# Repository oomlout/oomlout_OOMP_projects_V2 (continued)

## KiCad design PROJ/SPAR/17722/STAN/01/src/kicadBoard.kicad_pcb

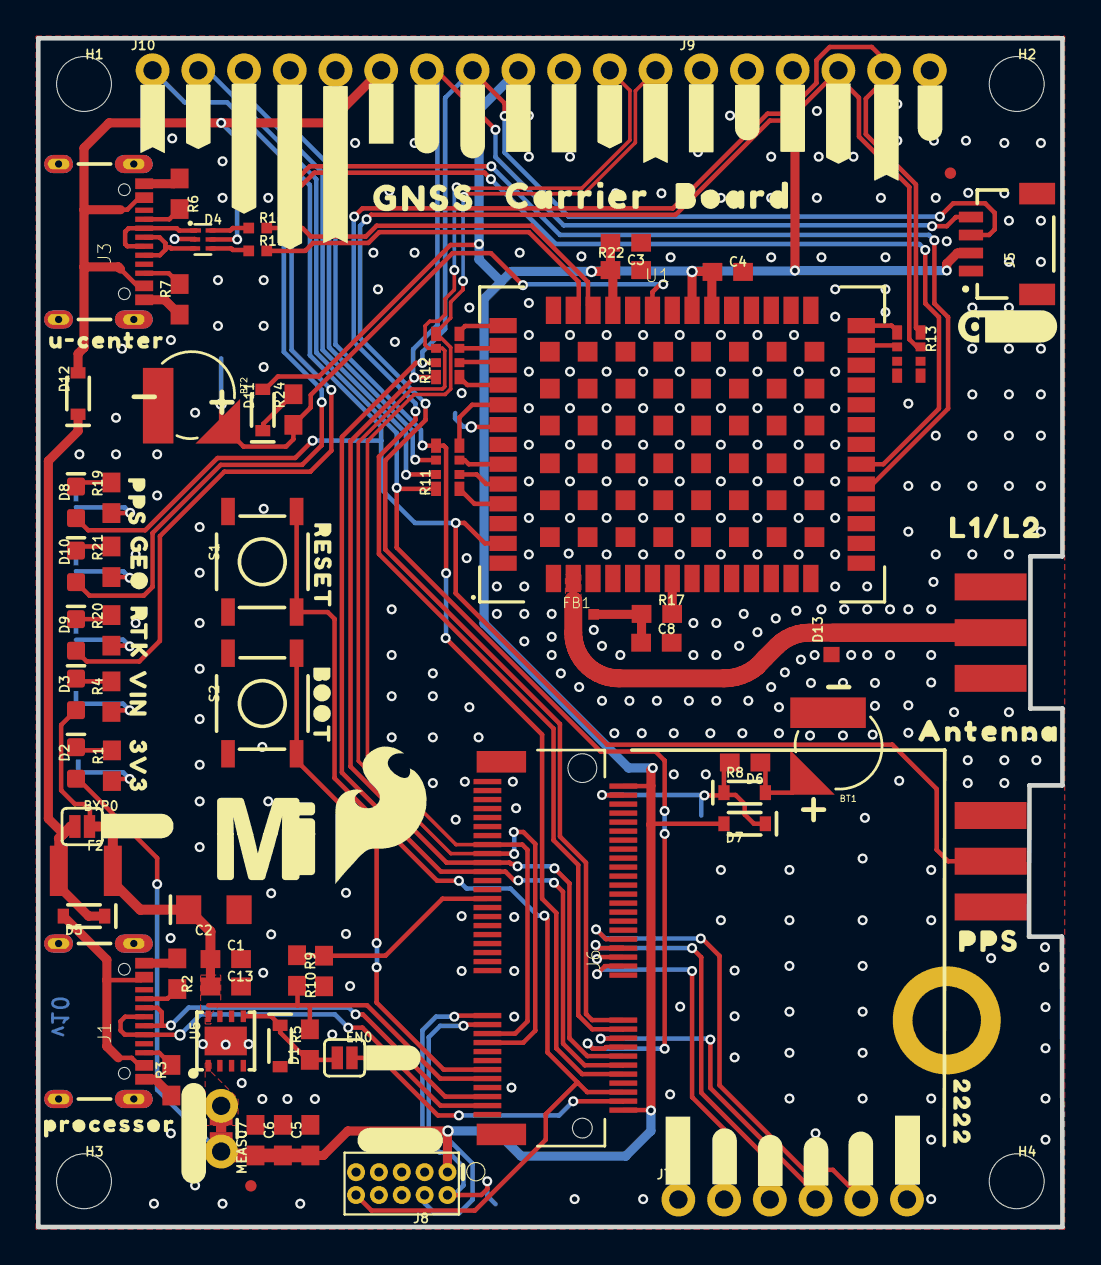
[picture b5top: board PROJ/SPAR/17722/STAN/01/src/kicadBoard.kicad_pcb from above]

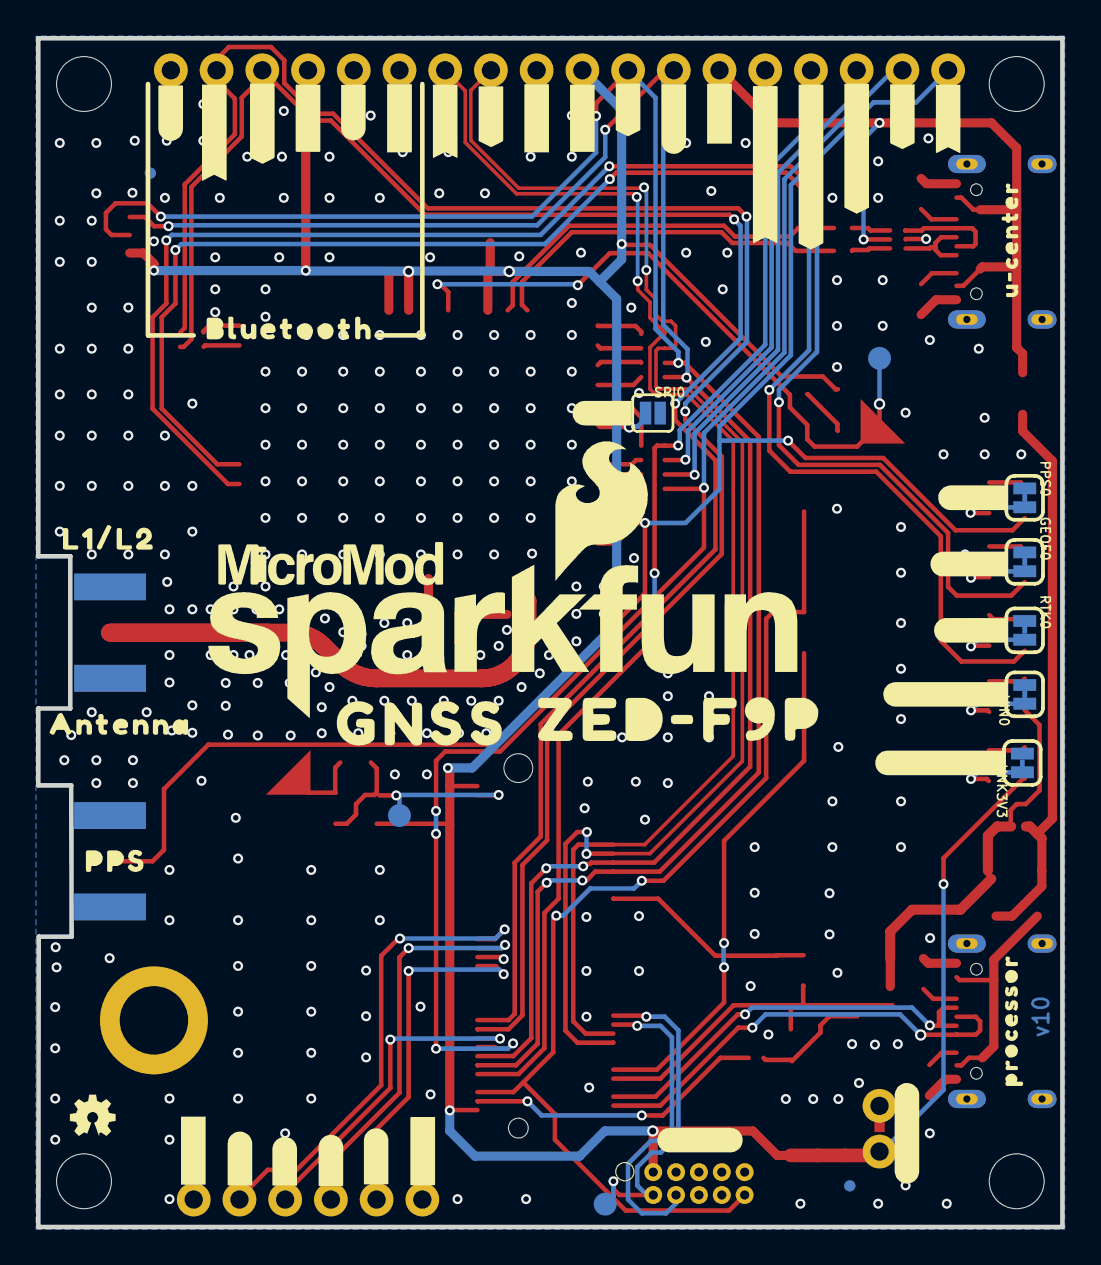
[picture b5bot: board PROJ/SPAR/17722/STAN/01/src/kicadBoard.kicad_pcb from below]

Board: 2 copper layers, 56.9 x 66.0 mm, 174 parts (54 on the bottom side), 71 nets.

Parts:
BT1: ML414H; ML414H_IV01E
BT2: ML414H_IV01E_BATTERY; ML414H_IV01E
BYP0: JUMPER-SMT_2_NO_SILK; SMT-JUMPER_2_NO_SILK
C1, C3, C4, C6: 0.1uF; 0603
C2: 10uF; EIA3216
C5: 1.0uF; 0603
C7, C13: 0.22uF; 0603
C8: 47pF; 0603
D1: 3.3V; SOD-323
D2, D3: RED; LED-0603
D4: PRTR5V0U2F; SOT886
D5, D6, D12: 3A/10V/280mV; SOD-323
D7: 1A/23V/620mV; SOD-323
D8, D9, D10: BLUE; LED-0603
D11: 0.5A/40V/420mV; SOD-323
D13: PESD0402; 0402
E1: ANTENNA-SMA-GROUNDEDEDGE_SMA; SMA-EDGE
EN0: JUMPER-SMT_2_NO_SILK; SMT-JUMPER_2_NO_SILK
F2: 6V/2A; 1210
FB1: FERRITE_BEAD-120_OHM-0402T; 0402-TIGHT
FD1, FD2, FD3, FD4: FIDUCIALUFIDUCIAL; FIDUCIAL-MICRO
FRAME1: FRAME-LEDGER; CREATIVE_COMMONS
GEOF0: JUMPER-SMT_2_NC_TRACE_SILK; SMT-JUMPER_2_NC_TRACE_SILK
H1, H2, H3, H4: STAND-OFFTIGHT; STAND-OFF-TIGHT
H5: STAND-OFF-REFLOW-M2.5_2.5MM_TALL; STAND-OFF-REFLOW-M2.5
J1, J3: USB-C-16P-2LAYER-PADS
J4: U.FL; SMA-EDGE
J5: QWIIC_RIGHT_ANGLE; JST04_1MM_RA
J6: MICROMOD-2222-C; M.2-CONNECTOR-E
J7, J9: 1X06_NO_SILK
J8: JTAG; 2X5-PTH-1.27MM
J10: 1X12_NO_SILK
LOGO1: SFE_LOGO_NAME_FLAME.3_INCH; SFE_LOGO_NAME_FLAME_.3
LOGO3: OSHW-LOGOMINI; OSHW-LOGO-MINI
MEAS0: JUMPER-COMBO_2_NC_TRACE; COMBO-JUMPER_2_NC_TRACE
PPS0: JUMPER-SMT_2_NC_TRACE_SILK; SMT-JUMPER_2_NC_TRACE_SILK
R1, R4, R8, R19, R20, R21: 1k; 0603
R2, R3, R6, R7: 5.1k; 0603
R5, R22: 100k; 0603
R9: 10k; 0603
R10: 20k; 0603
R11, R12, R13: 33; 1206_RA
R15, R16: 27OHM; 0402-TIGHT
R17: 33; 0603
R24: 3.3k; 0603
RTK0: JUMPER-SMT_2_NC_TRACE_SILK; SMT-JUMPER_2_NC_TRACE_SILK
S1: Reset; TACTILE_SWITCH_SMD_5.2MM
S2: BOOT; TACTILE_SWITCH_SMD_5.2MM
SPI0: JUMPER-SMT_2_NO_SILK; SMT-JUMPER_2_NO_SILK
TP1, TP2, TP3: TEST-POINT3X5; PAD.03X.05
U1: U-BLOX_ZED-F9P; ZED-F9P
U5: AP7361C-33; UDFN-8
U$1: ##SFBOOT##13
U$2: ##SFBOOT##8
U$3, U$4, U$31, U$32: #3V3#1
U$5: #RESET10
U$6, U$7, U$33, U$34, U$64, U$65, U$66, U$77, U$78: #GND#0
U$8: ##TX_READY##13
U$9: #PPS#6
U$10: #SCL#1
U$11: #RXI2#9
U$12: #SDA#0
U$13: #TXO#5
U$14: #RXI#6
U$15: #TXO2#9
U$16: PPS15
U$17, U$35: #VIN#13
U$18: GEO15
U$19: PPS14
U$20: RTK16
U$21: ANTENNA16
U$22: L1#L216
U$23: #GEO#9
U$24: ##TX_READY##7
U$25: MICROMOD_LOGO_.5
U$26: #PPS#10
U$27: #RTK#8
U$28: ##CS##9
U$29: #INT#4
U$30: #SPI#11
U$36: #INT#10
U$37: #PPS#3
U$38: #TXO2#10
U$39: #BYP#8
U$40: #RXI2#10
U$41: MICROMOD_MI_LOGO_1
U$42, U$132: #MEAS#10
U$43: BOOT10
U$44: ZED#F9P19
U$45: GNSS21
U$46: #CLK#7
U$47: #SDO#9
U$48: #EN#0
U$49: U#CENTER20
U$50: QWIIC_5.5MM
U$51, U$131: #SWD#10
U$52, U$73: PROCESSOR23
U$53: #SDI#11
U$54: BLUETOOTH24
U$55, U$83: #NC#4
U$56: U#CENTER22
U$57: #A0#14
U$58: L1#L217
U$59: ANTENNA17
U$60: PPS16
U$61: ##ZED_RESET##9
U$62: ##ZED_RESET##14
U$63: SFE_LOGO_FLAME_.3
U$67: #A0#8
U$68: VIN3
U$69: 3V34
U$70: #A1#8
U$71: #D1#8
U$72: #D2#8
U$74: #A1#14
U$75: #D1#14
U$76: #D2#14
U$79: GNSS501
U$80: CARRIER502
U$81: BOARD503
U$82: 2222501
U$84, U$85: #NC#5
U$133: #VIN_LED#10
U$134: #3V3_LED#10
UNK3V3: JUMPER-SMT_2_NC_TRACE_SILK; SMT-JUMPER_2_NC_TRACE_SILK
VIN0: JUMPER-SMT_2_NC_TRACE_SILK; SMT-JUMPER_2_NC_TRACE_SILK

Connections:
3.3V: C3.1, C4.1, C5.1, C6.1, C7.1, D2.A, D7.A, D11.A, J5.2, J6.2, J6.74, J8.1, J9.3, J10.9, MEAS0.2, MEAS0.4, R22.2, U1.33, U1.34, U1.38
3.3V_EN: D1.C, EN0.1, R5.1, U5.5
A0: J6.34, J7.2
A1: J6.38, J7.3
D1: J6.18, J7.4
D_SEL: SPI0.1, U1.47
G0/D2: J6.40, J7.5
GEO_STAT: D10.A, U1.19
GND: BT1.-, BT2.-, C1.2, C2.-, C3.2, C4.2, C5.2, C6.2, C7.2, C8.2, C13.2, D1.A, D4.2, D13.1, E1.GND@0, E1.GND@1, E1.GND@2, E1.GND@3, GEOF0.1, H5.1, J1.GND, J1.GND2, J3.GND, J3.GND2, J4.GND@0, J4.GND@1, J4.GND@2, J4.GND@3, J5.1, J6.1, J6.7, J6.33, J6.36, J6.39, J6.45, J6.75, J7.1, J7.6, J8.3, J8.5, J8.9, J9.1, J10.10, PPS0.1, R2.1, R3.1, R6.1, R7.1, R9.1, R22.1, RTK0.1, S1.1, S1.2, S2.1, S2.2, SPI0.2, U1.1, U1.3, U1.12, U1.14, U1.32, U1.37, U1.41, U1.48, U1.55, U1.56, U1.57, U1.58, U1.59, U1.60, U1.61, U1.62, U1.63, U1.64, U1.65, U1.66, U1.67, U1.68, U1.69, U1.70, U1.71, U1.72, U1.73, U1.74, U1.75, U1.76, U1.77, U1.78, U1.79, U1.80, U1.81, U1.82, U1.83, U1.84, U1.85, U1.86, U1.87, U1.88, U1.89, U1.90, U1.91, U1.92, U1.93, U1.94, U1.95, U1.96, U1.97, U1.98, U1.99, U1.100, U1.101, U1.102, U5.4, U5.EP, UNK3V3.2, VIN0.2
INT: J6.16, J10.2, R11.P8
unnamed: D2.C, R1.2
unnamed: R4.1, VIN0.1
unnamed: R1.1, UNK3V3.1
unnamed: D3.C, R4.2
unnamed: EN0.2, J6.4
unnamed: J3.A5, R6.2
unnamed: J3.B5, R7.2
unnamed: R20.1, RTK0.2
unnamed: D4.6, R16.1
unnamed: J1.A5, R2.2
unnamed: J1.B5, R3.2
unnamed: D4.3, J3.A6, J3.B6
unnamed: D4.1, J3.A7, J3.B7
unnamed: BT1.+, D6.A, R8.1
unnamed: R11.P1, U1.51
unnamed: R11.P2, U1.50
unnamed: D4.4, R15.1
unnamed: C8.1, FB1.2, R17.1
unnamed: R11.P3, U1.49
unnamed: R11.P4, U1.46
unnamed: R12.P1, U1.45
unnamed: R12.P2, U1.44
unnamed: R12.P3, U1.43
unnamed: R12.P4, U1.42
unnamed: R13.P1, U1.27
unnamed: R13.P2, U1.26
unnamed: PPS0.2, R19.1
unnamed: D8.C, R19.2
unnamed: D9.C, R20.2
unnamed: D11.C, R24.2
unnamed: GEOF0.2, R21.1
unnamed: D10.C, R21.2
OUT_MEAS: MEAS0.1, MEAS0.3, U5.1
PPS: D8.A, E1.SIG, J10.1, U1.53
RF_IN: D13.2, FB1.1, J4.SIG, U1.2
RTC_3V: D6.C, D7.C, J6.72, R8.2, TP1.1
RTK_STAT: D9.A, U1.20
RXI2: J6.22, J9.4, R13.P7
RXI/SDI: J6.17, J6.59, J10.11, R12.P6
SCL/SCK: J5.4, J6.14, J6.57, J10.7, R12.P8
SDA/~CS: J5.3, J6.12, J6.55, J10.8, R12.P7
SWDCK: J6.21, J8.4
SWDIO: J6.23, J8.2, TP2.1
TXO2: J6.20, J9.5, R13.P8
TXO/SDO: J6.19, J6.61, J10.12, R12.P5
TX_READY: J6.10, J10.5, R11.P5
USB_N: J1.A7, J1.B7, J6.5
USB_P: J1.A6, J1.B6, J6.3
VIN: BYP0.2, C1.1, C2.+, C13.1, D3.A, F2.2, J6.9, R5.2, R10.2, U5.8
VIN/3: J6.49, R9.2, R10.1
V_BATT: BT2.+, R24.1, TP3.1, U1.36
V_FUSE: BYP0.1, D5.C, D12.C, F2.1
V_RF: R17.2, U1.7
V_USB: D5.A, J1.VBUS1, J1.VBUS2
V_USB_2: D4.5, D12.A, J3.VBUS1, J3.VBUS2, J10.6
ZED_USB_N: R16.2, U1.39
ZED_USB_P: R15.2, U1.40
~BOOT: J6.11, S2.3, S2.4
~RESET: J6.6, J8.10, S1.3, S1.4
~SAFEBOOT: J10.3, R11.P7
~ZED_RESET: J10.4, R11.P6

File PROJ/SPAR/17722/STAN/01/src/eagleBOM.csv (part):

"Part";"Value";"Device";"Package";"Description";"DESIGNER";"DIGIKEY_PART";"MOUSE_PART";"PROD_ID";"REV";"VALUE";
"3V3";"JUMPER-SMT_2_NC_TRACE_SILK";"JUMPER-SMT_2_NC_TRACE_SILK";"SMT-JUMPER_2_NC_TRACE_SILK";"Normally closed trace jumper";"";"";"";"";"";"";
"BT1";"ML414H";"ML414H_IV01E_BATTERY";"ML414H_IV01E";"SEIKO ML414H-IV01E Reflowable Lithium Battery";"";"";"";"BATT-14267";"";"";
"BT2";"ML414H_IV01E_BATTERY";"ML414H_IV01E_BATTERY";"ML414H_IV01E";"SEIKO ML414H-IV01E Reflowable Lithium Battery";"";"";"";"BATT-14267";"";"";
"BYP";"JUMPER-SMT_2_NO_SILK";"JUMPER-SMT_2_NO_SILK";"SMT-JUMPER_2_NO_SILK";"Normally open jumper";"";"";"";"";"";"";
"C1";"0.1uF";"0.1UF-0603-25V-(+80/-20%)";"0603";"0.1µF ceramic capacitors";"";"";"";"CAP-00810";"";"0.1uF";
"C2";"10uF";"10UF-POLAR-EIA3216-16V-10%(TANT)";"EIA3216";"10.0µF polarized capacitors";"";"";"";"CAP-00811";"";"10uF";
"C3";"0.1uF";"0.1UF-0603-25V-5%";"0603";"0.1µF ceramic capacitors";"";"";"";"CAP-08604";"";"0.1uF";
"C4";"0.1uF";"0.1UF-0603-25V-5%";"0603";"0.1µF ceramic capacitors";"";"";"";"CAP-08604";"";"0.1uF";
"C5";"1.0uF";"1.0UF-0603-16V-10%";"0603";"1µF ceramic capacitors";"";"";"";"CAP-00868";"";"1.0uF";
"C6";"0.1uF";"0.1UF-0603-25V-(+80/-20%)";"0603";"0.1µF ceramic capacitors";"";"";"";"CAP-00810";"";"0.1uF";
"C7";"0.22uF";"0.22UF-0603-25V-10%";"0603";"0.22µF ceramic capacitors";"";"";"";"CAP-07822";"";"0.22uF";
"C8";"47pF";"47PF-0603-50V-5%";"0603";"47pF ceramic capacitors";"";"";"";"CAP-08913";"";"47pF";
"C13";"0.22uF";"0.22UF-0603-25V-10%";"0603";"0.22µF ceramic capacitors";"";"";"";"CAP-07822";"";"0.22uF";
"D1";"3.3V";"DIODE-ZENER-MM3Z3V3T1G";"SOD-323";"Zener Diode";"";"";"";"DIO-11284";"";"3.3V";
"D2";"RED";"LED-RED0603";"LED-0603";"Red SMD LED";"";"";"";"DIO-00819";"";"RED";
"D3";"RED";"LED-RED0603";"LED-0603";"Red SMD LED";"";"";"";"DIO-00819";"";"RED";
"D4";"PRTR5V0U2F";"PRTR5V0U2F";"SOT886";"A small ESD protection device. Most commonly used on USB D+/D- signals to protect large, expensive, or especially sensitive USB enabled devices.";"";"";"";"DIO-14084";"";"";
"D5";"3A/10V/280mV";"DIODE-SCHOTTKY-BAT60A";"SOD-323";"Schottky diode";"";"";"";"DIO-14072";"";"3A/10V/280mV";
"D6";"3A/10V/280mV";"DIODE-SCHOTTKY-BAT60A";"SOD-323";"Schottky diode";"";"";"";"DIO-14072";"";"3A/10V/280mV";
"D7";"1A/23V/620mV";"DIODE-SCHOTTKY-BAT20J";"SOD-323";"Schottky diode";"";"";"";"DIO-11623";"";"1A/23V/620mV";
"D8";"BLUE";"LED-BLUE0603";"LED-0603";"Blue SMD LED";"";"";"";"DIO-08575";"";"BLUE";
"D9";"BLUE";"LED-BLUE0603";"LED-0603";"Blue SMD LED";"";"";"";"DIO-08575";"";"BLUE";
"D10";"BLUE";"LED-BLUE0603";"LED-0603";"Blue SMD LED";"";"";"";"DIO-08575";"";"BLUE";
"D11";"0.5A/40V/420mV";"DIODE-SCHOTTKY-PMEG4005EJ";"SOD-323";"Schottky diode";"";"";"";"DIO-10955";"";"0.5A/40V/420mV";
"D12";"3A/10V/280mV";"DIODE-SCHOTTKY-BAT60A";"SOD-323";"Schottky diode";"";"";"";"DIO-14072";"";"3A/10V/280mV";
"D13";"PESD0402";"PESD0402";"0402";"ESD protection diode";"";"PESD0402-140CT-ND";"650-PESD0402-140";"DIO-15359";"";"";
"E1";"ANTENNA-SMA-GROUNDEDEDGE_SMA";"ANTENNA-SMA-GROUNDEDEDGE_SMA";"SMA-EDGE";"SMA Antenna Connector w/ Ground";"";"";"";"CONN-08289";"";"";
"EN";"JUMPER-SMT_2_NO_SILK";"JUMPER-SMT_2_NO_SILK";"SMT-JUMPER_2_NO_SILK";"Normally open jumper";"";"";"";"";"";"";
"F2";"6V/2A";"PPTC_6V2A";"1210";"Resettable Fuse PPTC";"";"";"";"RES-14313";"";"6V/2A";
"FB1";"FERRITE_BEAD-120_OHM-0402T";"FERRITE_BEAD-120_OHM-0402T";"0402-TIGHT";"Ferrite Bead (blocks, cores, rings, chokes, etc.)";"";"";"";"NDUC-14206";"";"";
"FD1";"FIDUCIALUFIDUCIAL";"FIDUCIALUFIDUCIAL";"FIDUCIAL-MICRO";"Fiducial Alignment Points";"";"";"";"";"";"";
"FD2";"FIDUCIALUFIDUCIAL";"FIDUCIALUFIDUCIAL";"FIDUCIAL-MICRO";"Fiducial Alignment Points";"";"";"";"";"";"";
"FD3";"FIDUCIALUFIDUCIAL";"FIDUCIALUFIDUCIAL";"FIDUCIAL-MICRO";"Fiducial Alignment Points";"";"";"";"";"";"";
"FD4";"FIDUCIALUFIDUCIAL";"FIDUCIALUFIDUCIAL";"FIDUCIAL-MICRO";"Fiducial Alignment Points";"";"";"";"";"";"";
"FRAME1";"FRAME-LEDGER";"FRAME-LEDGER";"CREATIVE_COMMONS";"Schematic Frame - Ledger";"";"";"";"";"";"";
"GEOF";"JUMPER-SMT_2_NC_TRACE_SILK";"JUMPER-SMT_2_NC_TRACE_SILK";"SMT-JUMPER_2_NC_TRACE_SILK";"Normally closed trace jumper";"";"";"";"";"";"";
"H1";"STAND-OFFTIGHT";"STAND-OFFTIGHT";"STAND-OFF-TIGHT";"Stand Off";"";"";"";"";"";"";
"H2";"STAND-OFFTIGHT";"STAND-OFFTIGHT";"STAND-OFF-TIGHT";"Stand Off";"";"";"";"";"";"";
"H3";"STAND-OFFTIGHT";"STAND-OFFTIGHT";"STAND-OFF-TIGHT";"Stand Off";"";"";"";"";"";"";
"H4";"STAND-OFFTIGHT";"STAND-OFFTIGHT";"STAND-OFF-TIGHT";"Stand Off";"";"";"";"";"";"";
"H5";"STAND-OFF-REFLOW-M2.5_2.5MM_TALL";"STAND-OFF-REFLOW-M2.5_2.5MM_TALL";"STAND-OFF-REFLOW-M2.5";"Stand Off Reflow Compatible";"";"";"";"HW-14899";"";"";
"J1";"";"USB_C_2-LAYER_PADS";"USB-C-16P-2LAYER-PADS";"USB Type C 16Pin Connector";"";"";"";"CONN-14122";"";"";
"J3";"";"USB_C_2-LAYER_PADS";"USB-C-16P-2LAYER-PADS";"USB Type C 16Pin Connector";"";"";"";"CONN-14122";"";"";
"J4";"U.FL";"ANTENNA-SMA-GROUNDEDEDGE_SMA";"SMA-EDGE";"SMA Antenna Connector w/ Ground";"";"";"";"CONN-08289";"";"";
"J5";"QWIIC_RIGHT_ANGLE";"QWIIC_CONNECTORJS-1MM";"JST04_1MM_RA";"SparkFun I2C Standard Qwiic Connector";"";"";"";"CONN-13694";"";"QWIIC_RIGHT_ANGLE";
"J6";"MICROMOD-2222-C";"MICROMOD-2222-C";"M.2-CONNECTOR-E";"MicroMod Connector";"";"";"";"CONN-14877";"";"";
"J7";"";"CONN_06NO_SILK_NO_POP";"1X06_NO_SILK";"Multi connection point. Often used as Generic Header-pin footprint for 0.1 inch spaced/style header connections";"";"";"";"";"";"";
"J8";"JTAG";"CORTEX_JTAG_DEBUG_MINIMUM_PTH";"2X5-PTH-1.27MM";"Cortex Debug Connector - 10 pin";"";"";"";"";"";"";
"J9";"";"CONN_06NO_SILK_NO_POP";"1X06_NO_SILK";"Multi connection point. Often used as Generic Header-pin footprint for 0.1 inch spaced/style header connections";"";"";"";"";"";"";
"J10";"";"CONN_12NO_SILK";"1X12_NO_SILK";"Multi connection point. Often used as Generic Header-pin footprint for 0.1 inch spaced/style header connections";"";"";"";"";"";"";
"LOGO1";"SFE_LOGO_NAME_FLAME.3_INCH";"SFE_LOGO_NAME_FLAME.3_INCH";"SFE_LOGO_NAME_FLAME_.3";"SparkFun Font Logo w/ Flame";"";"";"";"";"";"";
"LOGO3";"OSHW-LOGOMINI";"OSHW-LOGOMINI";"OSHW-LOGO-MINI";"Open-Source Hardware (OSHW) Logo";"";"";"";"";"";"";
"MEAS";"JUMPER-COMBO_2_NC_TRACE";"JUMPER-COMBO_2_NC_TRACE";"COMBO-JUMPER_2_NC_TRACE";"";"";"";"";"";"";"";
"PPS";"JUMPER-SMT_2_NC_TRACE_SILK";"JUMPER-SMT_2_NC_TRACE_SILK";"SMT-JUMPER_2_NC_TRACE_SILK";"Normally closed trace jumper";"";"";"";"";"";"";
"R1";"1k";"1KOHM-0603-1/10W-1%";"0603";"1kΩ resistor";"";"";"";"RES-07856";"";"1k";
"R2";"5.1k";"5.1KOHM5.1KOHM-0603-1/10W-1%";"0603";"";"";"";"";"RES-12083";"";"5.1k";
"R3";"5.1k";"5.1KOHM5.1KOHM-0603-1/10W-1%";"0603";"";"";"";"";"RES-12083";"";"5.1k";
"R4";"1k";"1KOHM-0603-1/10W-1%";"0603";"1kΩ resistor";"";"";"";"RES-07856";"";"1k";
"R5";"100k";"100KOHM-0603-1/10W-1%";"0603";"100kΩ resistor";"";"";"";"RES-07828";"";"100k";
"R6";"5.1k";"5.1KOHM5.1KOHM-0603-1/10W-1%";"0603";"";"";"";"";"RES-12083";"";"5.1k";
"R7";"5.1k";"5.1KOHM5.1KOHM-0603-1/10W-1%";"0603";"";"";"";"";"RES-12083";"";"5.1k";
"R8";"1k";"1KOHM-0603-1/10W-1%";"0603";"1kΩ resistor";"";"";"";"RES-07856";"";"1k";
"R9";"10k";"10KOHM-0603-1/10W-1%";"0603";"10kΩ resistor";"";"";"";"RES-00824";"";"10k";
"R10";"20k";"20KOHM-0603-1/10W-1%";"0603";"20kΩ resistor";"";"";"";"RES-09383";"";"20k";
"R11";"33";"33OHM_RA-1206-1/16W-5%";"1206_RA";"EXB-38V330JV";"";"";"";"RES-15081";"";"33";
"R12";"33";"33OHM_RA-1206-1/16W-5%";"1206_RA";"EXB-38V330JV";"";"";"";"RES-15081";"";"33";
"R13";"33";"33OHM_RA-1206-1/16W-5%";"1206_RA";"EXB-38V330JV";"";"";"";"RES-15081";"";"33";
"R15";"27OHM";"27OHM";"0402-TIGHT";"27Ω resistor";"";"";"";"RES-15238";"";"";
"R16";"27OHM";"27OHM";"0402-TIGHT";"27Ω resistor";"";"";"";"RES-15238";"";"";
"R17";"33";"33OHM-0603-1/10W-1%";"0603";"33Ω resistor";"";"";"";"RES-08270";"";"33";
"R19";"1k";"1KOHM-0603-1/10W-1%";"0603";"1kΩ resistor";"";"";"";"RES-07856";"";"1k";
"R20";"1k";"1KOHM-0603-1/10W-1%";"0603";"1kΩ resistor";"";"";"";"RES-07856";"";"1k";
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
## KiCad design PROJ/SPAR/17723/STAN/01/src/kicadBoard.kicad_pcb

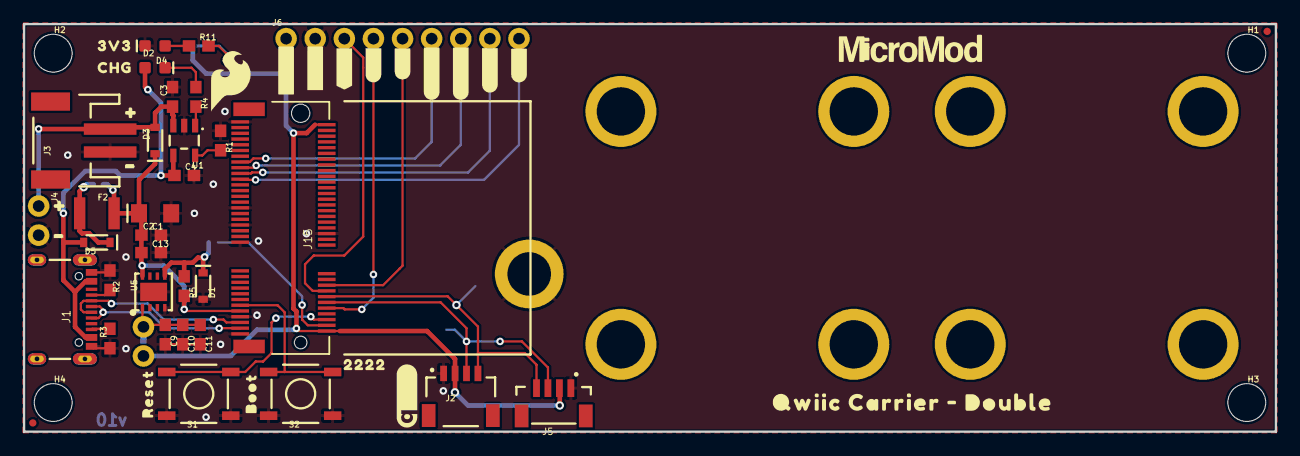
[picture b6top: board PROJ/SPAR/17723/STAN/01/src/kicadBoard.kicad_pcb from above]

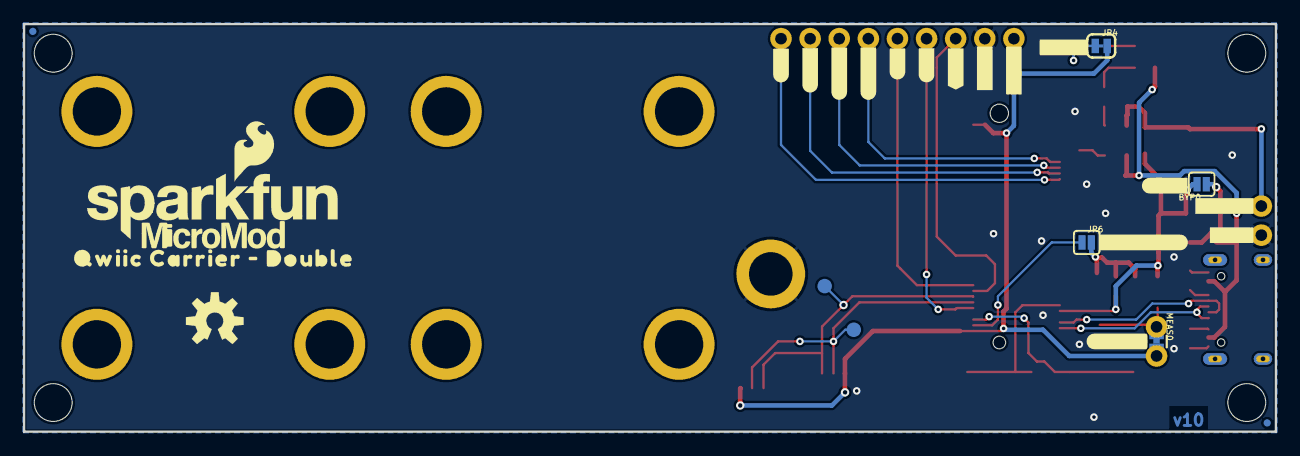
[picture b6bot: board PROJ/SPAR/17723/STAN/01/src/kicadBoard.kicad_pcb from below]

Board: 2 copper layers, 109.2 x 35.6 mm, 90 parts (27 on the bottom side), 29 nets.

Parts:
BYP0: JUMPER-SMT_2_NO_SILK; SMT-JUMPER_2_NO_SILK
C1: 0.1uF; 0603
C2: 10uF; EIA3216
C3, C4: 4.7uF; 0603
C9: 10uF; 0603
C10: 1.0uF; 0603
C11, C13: 0.22uF; 0603
D1: 3.3V; SOD-323
D2: RED; LED-0603
D3, D5: 3A/10V/280mV; SOD-323
D4: Yellow; LED-0603
F2: 6V/2A; 1210
FD1, FD2, FD3, FD4: FIDUCIALUFIDUCIAL; FIDUCIAL-MICRO
FRAME1: FRAME-LEDGER; CREATIVE_COMMONS
H1, H2, H3, H4: STAND-OFF
H5: STAND-OFF-REFLOW2.5MM_TALL; STAND-OFF-REFLOW-M2.5
J1: USB-C-16P-2LAYER-PADS
J2: QWIIC_RIGHT_ANGLE; JST04_1MM_RA
J3: JST-2-SMD
J4: 1X02_NO_SILK
J5: Vertical Qwiic Connector; JST04_1MM_VERT
J6: 1X09_NO_SILK
J15: MICROMOD-2222-C; M.2-CONNECTOR-E
JP4: 3V3 LED; SMT-JUMPER_2_NC_TRACE_SILK
JP6: VE; SMT-JUMPER_2_NO_SILK
LOGO1: SFE_LOGO_NAME_FLAME.2_INCH; SFE_LOGO_NAME_FLAME_.2
LOGO2: QWIIC_LOGO_CONNECTOR; QWIIC_5.5MM
LOGO3: OSHW-LOGOM; OSHW-LOGO-M
MEAS0: COMBO-JUMPER_2_NC_TRACE
R1: 2.2k; 0603
R2, R3: 5.1k; 0603
R4, R11: 1k; 0603
R5: 100k; 0603
S1: Reset; TACTILE_SWITCH_SMD_5.2MM
S2: BOOT; TACTILE_SWITCH_SMD_5.2MM
TP1, TP2: TEST-POINT3X5; PAD.03X.05
U1: MCP73831; SOT23-5
U5: AP7361C-33FGEUDFN-8; UDFN-8
U$1: #3#3V_EN#0
U$2, U$5: QWIIC_BOARD_OUTLINESTANDOFF; QWIIC_BOARD_MOUNT_SMD_STANDOFFS
U$3: 3V30
U$4: CHG0
U$6, U$35, U$38: #3#3V#0
U$7: #BYP#0
U$8, U$14, U$33: #GND#0
U$9: #MEAS#0
U$10, U$13: QWIIC_CARRIER_#_DOUBLE0
U$11, U$32, U$36, U$37: #0
U$12: #VBAT#0
U$15, U$16: ##INT##0
U$17, U$18: #D0#0
U$20, U$21: #D1#0
U$22, U$23: #CIPO#0
U$24, U$25: #COPI#0
U$26, U$27: #SCK#0
U$28, U$29: ##CS##0
U$30: RESET0
U$31: BOOT0
U$34: 22220
U$44: SFE_LOGO_FLAME_.2
U$67, U$68: MICROMOD_LOGO_.5

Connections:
3.3V: J2.2, J5.2, J6.1, J15.2, J15.74, JP4.2, MEAS0.2, MEAS0.4
3.3V_EN: J15.4, JP6.1
D0: J6.4, J15.10
D1: J6.5, J15.18
GND: C1.2, C2.-, C3.2, C4.2, C9.2, C10.2, C11.2, C13.2, D1.A, D2.C, H5.1, J1.GND, J1.GND2, J2.1, J3.1, J4.2, J5.1, J6.2, J15.1, J15.7, J15.33, J15.36, J15.39, J15.45, J15.75, R1.1, R2.1, R3.1, S1.1, S1.2, S2.1, S2.2, U1.2, U5.4, U5.EP
I2C_~INT: J6.3, J15.16
unnamed: C9.1, C10.1, C11.1, MEAS0.1, MEAS0.3, U5.1
unnamed: R1.2, U1.5
unnamed: D4.C, R4.1
unnamed: JP4.1, R11.2
unnamed: D2.A, R11.1
unnamed: R4.2, U1.1
unnamed: J1.A5, R2.2
unnamed: J1.B5, R3.2
SCL: J2.4, J5.4, J15.14, TP2.P$1
SDA: J2.3, J5.3, J15.12, TP1.P$1
SPI_CIPO: J6.6, J15.61
SPI_COPI: J6.7, J15.59
SPI_SCK: J6.8, J15.57
SPI_~CS: J6.9, J15.55
USB_D+: J1.A6, J1.B6, J15.3
USB_D-: J1.A7, J1.B7, J15.5
VIN: BYP0.2, C1.1, C2.+, C13.1, D3.C, F2.2, J15.9, R5.2, U5.8
VREG_EN: D1.C, JP6.2, R5.1, U5.5
V_BATT: C3.1, D3.A, J3.2, J4.1, U1.3
V_USB: C4.1, D4.A, D5.A, J1.VBUS1, J1.VBUS2, U1.4
V_USB_2: BYP0.1, D5.C, F2.1
~BOOT: J15.11, S2.3, S2.4
~RESET: J15.6, S1.3, S1.4

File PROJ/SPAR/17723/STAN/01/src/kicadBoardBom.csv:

"Id";"Designator";"Package";"Quantity";"Designation";"Supplier and ref";
1;"D1";"SOD-323";1;"3.3V";;;
2;"FD2,FD1,FD4,FD3";"FIDUCIAL-MICRO";4;"FIDUCIALUFIDUCIAL";;;
3;"F2";"1210";1;"6V/2A";;;
4;"U$5,U$2";"QWIIC_BOARD_MOUNT_SMD_STANDOFFS";2;"QWIIC_BOARD_OUTLINESTANDOFF";;;
5;"H5";"STAND-OFF-REFLOW-M2.5";1;"STAND-OFF-REFLOW2.5MM_TALL";;;
6;"J15";"M.2-CONNECTOR-E";1;"MICROMOD-2222-C";;;
7;"U5";"UDFN-8";1;"AP7361C-33FGEUDFN-8";;;
8;"R2,R3";"0603";2;"5.1k";;;
9;"R1";"0603";1;"2.2k";;;
10;"U$36,U$32,U$37,U$11";"#0";4;"";;;
11;"R11,R4";"0603";2;"1k";;;
12;"U$35,U$38,U$6";"#3#3V#0";3;"";;;
13;"C9";"0603";1;"10uF";;;
14;"H1,H4,H2,H3";"STAND-OFF";4;"STAND-OFF";;;
15;"U$17,U$18";"#D0#0";2;"";;;
16;"J4";"1X02_NO_SILK";1;"";;;
17;"J5";"JST04_1MM_VERT";1;"Vertical Qwiic Connector";;;
18;"U$44";"SFE_LOGO_FLAME_.2";1;"";;;
19;"D2";"LED-0603";1;"RED";;;
20;"C3,C4";"0603";2;"4.7uF";;;
21;"U$20,U$21";"#D1#0";2;"";;;
22;"C2";"EIA3216";1;"10uF";;;
23;"D3,D5";"SOD-323";2;"3A/10V/280mV";;;
24;"C13,C11";"0603";2;"0.22uF";;;
25;"U$15,U$16";"##INT##0";2;"";;;
26;"U$3";"3V30";1;"";;;
27;"LOGO2";"QWIIC_5.5MM";1;"QWIIC_LOGO_CONNECTOR";;;
28;"U$22,U$23";"#CIPO#0";2;"";;;
29;"U$28,U$29";"##CS##0";2;"";;;
30;"D4";"LED-0603";1;"Yellow";;;
31;"S1";"TACTILE_SWITCH_SMD_5.2MM";1;"Reset";;;
32;"U1";"SOT23-5";1;"MCP73831";;;
33;"U$4";"CHG0";1;"";;;
34;"J3";"JST-2-SMD";1;"";;;
35;"U$30";"RESET0";1;"";;;
36;"U$26,U$27";"#SCK#0";2;"";;;
37;"J1";"USB-C-16P-2LAYER-PADS";1;"";;;
38;"U$34";"22220";1;"";;;
39;"S2";"TACTILE_SWITCH_SMD_5.2MM";1;"BOOT";;;
40;"J6";"1X09_NO_SILK";1;"";;;
41;"C1";"0603";1;"0.1uF";;;
42;"U$8,U$33,U$14";"#GND#0";3;"";;;
43;"U$10,U$13";"QWIIC_CARRIER_#_DOUBLE0";2;"";;;
44;"R5";"0603";1;"100k";;;
45;"J2";"JST04_1MM_RA";1;"QWIIC_RIGHT_ANGLE";;;
46;"U$31";"BOOT0";1;"";;;
47;"U$24,U$25";"#COPI#0";2;"";;;
48;"FRAME1";"CREATIVE_COMMONS";1;"FRAME-LEDGER";;;
49;"U$67,U$68";"MICROMOD_LOGO_.5";2;"";;;
50;"C10";"0603";1;"1.0uF";;;
51;"U$9";"#MEAS#0";1;"";;;
52;"JP6";"SMT-JUMPER_2_NO_SILK";1;"VE";;;
53;"U$1";"#3#3V_EN#0";1;"";;;
54;"MEAS0";"COMBO-JUMPER_2_NC_TRACE";1;"";;;
55;"BYP0";"SMT-JUMPER_2_NO_SILK";1;"JUMPER-SMT_2_NO_SILK";;;
56;"U$12";"#VBAT#0";1;"";;;
57;"JP4";"SMT-JUMPER_2_NC_TRACE_SILK";1;"3V3 LED";;;
58;"TP1,TP2";"PAD.03X.05";2;"TEST-POINT3X5";;;
59;"LOGO1";"SFE_LOGO_NAME_FLAME_.2";1;"SFE_LOGO_NAME_FLAME.2_INCH";;;
60;"LOGO3";"OSHW-LOGO-M";1;"OSHW-LOGOM";;;
61;"U$7";"#BYP#0";1;"";;;

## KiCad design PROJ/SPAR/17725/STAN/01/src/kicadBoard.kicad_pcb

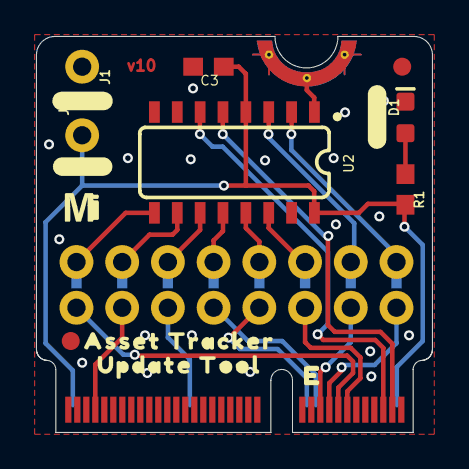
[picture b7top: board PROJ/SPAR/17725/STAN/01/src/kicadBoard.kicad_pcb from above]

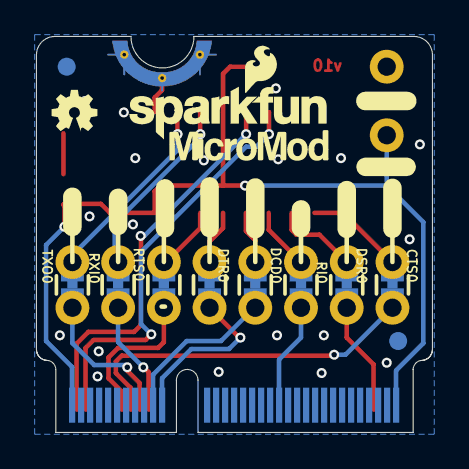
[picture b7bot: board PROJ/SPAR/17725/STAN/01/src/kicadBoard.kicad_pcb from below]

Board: 4 copper layers, 22.0 x 22.0 mm, 40 parts (23 on the bottom side), 21 nets.

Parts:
C3: 0.1uF; 0603
CTS0: JUMPER-COMBO_2_NC_TRACE; COMBO-JUMPER_2_NC_TRACE
D1: BLUE; LED-0603
DCD0: JUMPER-COMBO_2_NC_TRACE; COMBO-JUMPER_2_NC_TRACE
DSR0: JUMPER-COMBO_2_NC_TRACE; COMBO-JUMPER_2_NC_TRACE
DTR0: JUMPER-COMBO_2_NC_TRACE; COMBO-JUMPER_2_NC_TRACE
FRAME1: FRAME-LETTER; CREATIVE_COMMONS
J1, J2: 1X01_NO_SILK
J5: MICROMOD-2222; M.2-CARD-E-22
JP3, JP4, JP5, JP6: FIDUCIAL1X2; FIDUCIAL-1X2
LOGO1: OSHW-LOGOMINI; OSHW-LOGO-MINI
LOGO2: SPECIAL_INSTRUCTIONS-ORDERING; ORDERING_INSTRUCTIONS
LOGO3: SFE_LOGO_NAME_FLAME.1_INCH; SFE_LOGO_NAME_FLAME_.1
R1: 1k; 0603
RI0: JUMPER-COMBO_2_NC_TRACE; COMBO-JUMPER_2_NC_TRACE
RTS0: JUMPER-COMBO_2_NC_TRACE; COMBO-JUMPER_2_NC_TRACE
RXI0: JUMPER-COMBO_2_NC_TRACE; COMBO-JUMPER_2_NC_TRACE
TXO0: JUMPER-COMBO_2_NC_TRACE; COMBO-JUMPER_2_NC_TRACE
U2: CH340C; SO016
U$1: #TX#0
U$2: #RX#0
U$3, U$7: #GND#2
U$4: #DTR#0
U$5: #RI#0
U$6, U$17: #3V3#3
U$8: #PWR#0
U$9: MICROMOD_MI_LOGO_.35
U$10: ASSET_TRACKER0
U$11: UPDATE_TOOL0
U$12: MICROMOD_LOGO_.35
U$14: #CTS#0
U$18: #DSR#0
U$20: #RTS#0
U$23: #DCD#0

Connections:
3.3V: C3.1, J2.1, J5.2, J5.74, R1.2, U2.4, U2.16
GND: C3.2, D1.C, J1.1, J5.1, J5.7, J5.33, J5.36, J5.39, J5.45, J5.75, J5.GND1, J5.GND2, J5.GND3, U2.1
unnamed: D1.A, R1.1
RXI: RXI0.1, RXI0.3, U2.3
SARA_CTS_O: CTS0.2, CTS0.4, J5.15
SARA_DCD_O: DCD0.2, DCD0.4, J5.20
SARA_DSR_O: DSR0.2, DSR0.4, J5.69
SARA_DTR_I: DTR0.2, DTR0.4, J5.22
SARA_RI_O: J5.48, RI0.2, RI0.4
SARA_RTS_I: J5.13, RTS0.2, RTS0.4
SARA_RXD_O: J5.19, RXI0.2, RXI0.4
SARA_TXD_I: J5.17, TXO0.2, TXO0.4
TXO: TXO0.1, TXO0.3, U2.2
USB_D+: J5.3, U2.5
USB_D-: J5.5, U2.6
~CTS_I: CTS0.1, CTS0.3, U2.9
~DCD_I: DCD0.1, DCD0.3, U2.12
~DSR_I: DSR0.1, DSR0.3, U2.10
~DTR_O: DTR0.1, DTR0.3, U2.13
~RI_I: RI0.1, RI0.3, U2.11
~RTS_O: RTS0.1, RTS0.3, U2.14

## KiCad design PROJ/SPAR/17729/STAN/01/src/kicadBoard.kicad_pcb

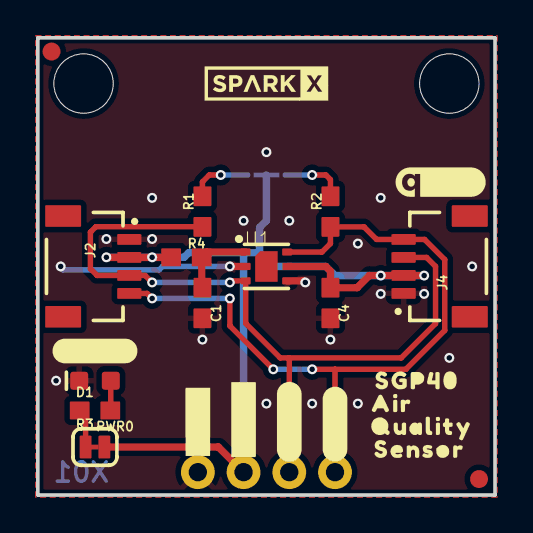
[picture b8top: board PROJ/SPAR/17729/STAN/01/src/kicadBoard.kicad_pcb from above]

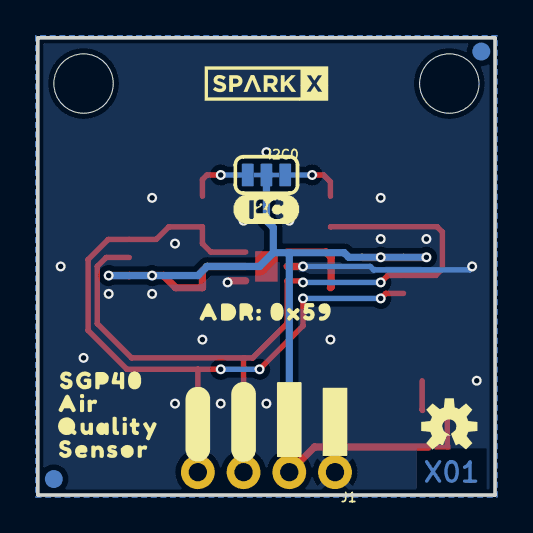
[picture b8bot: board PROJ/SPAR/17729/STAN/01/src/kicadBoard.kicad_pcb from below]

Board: 2 copper layers, 25.4 x 25.4 mm, 44 parts (16 on the bottom side), 9 nets.

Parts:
C1, C4: 1.0uF; 0603
D1: RED; LED-0603
FRAME1: FRAME-LETTER; CREATIVE_COMMONS
I2C0: JUMPER-SMT_3_2-NC_TRACE_SILK; SMT-JUMPER_3_2-NC_TRACE_SILK
J1: 1X04_NO_SILK
J2, J4: QWIIC_RIGHT_ANGLE; JST04_1MM_RA
JP1, JP2, JP5, JP6: FIDUCIAL1X2; FIDUCIAL-1X2
JP3, JP4: STAND-OFF
LOGO1: SPECIAL_INSTRUCTIONS-ORDERING; ORDERING_INSTRUCTIONS
LOGO5: OSHW-LOGOS; OSHW-LOGO-S
PWR0: JUMPER-SMT_2_NC_TRACE_SILK; SMT-JUMPER_2_NC_TRACE_SILK
R1, R2: 10k; 0603
R3: 1k; 0603
R4: 4.7; 0603
U1: SGP40
U$1, U$33: #GND#0
U$2, U$34: #3#3V#0
U$3, U$35: #SDA#0
U$4, U$36: #SCL#0
U$10, U$18: SPARKX-LOGO3; SPARKX-SMALL
U$15: I2C
U$16: QWIIC_5MM
U$19, U$20: SGP400
U$23, U$24: AIR0
U$25, U$28: QUALITY0
U$29, U$30: SENSOR0
U$31: ADR#_0X590
U$32: #PWR#0

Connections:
3.3V: C4.1, I2C0.2, J1.2, J2.2, J4.2, PWR0.2, R4.1, U1.5
GND: C1.2, C4.2, D1.C, J1.1, J2.1, J4.1, U1.2, U1.4, U1.DIEPAD
unnamed: PWR0.1, R3.2
unnamed: I2C0.3, R1.2
unnamed: D1.A, R3.1
unnamed: I2C0.1, R2.2
unnamed: C1.1, R4.2, U1.1
SCL: J1.4, J2.4, J4.4, R2.1, U1.6
SDA: J1.3, J2.3, J4.3, R1.1, U1.3
